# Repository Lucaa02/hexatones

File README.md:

# HEXATONES
Hexatones was born from a simple idea: to break the synthesizer down into its fundamental modules—from power supplies to VCAs, ADSR envelopes, and even guitar pedals.

Full **flexibility** is the key to discovering entirely new sounds. By stacking, cascading, and inverting modules, or by relying on smaller, granular building blocks rather than rigid, all-in-one units, Hexatones empowers musicians to explore uncharted sonic territory. 

## Open Hardware

Everybody has the right to now why and how a sound is produced. 

## Analog is Key, Digital could help

Hexatones embraces the beautiful imperfections of **analog hardware**: circuit inaccuracies, thermal drift, and the subtle inductance introduced by wiring. We reject the dullness of perfectly predictable sound. Instead, the philosophy is to lean into the system, tune into its quirks, and turn those "errors" into features to create something genuinely **unique** every single time.

## Schematics, Layout, and Panelization
Keeping costs low is a core priority. Every design is optimized to leverage **affordable** PCB fabrication services and standard component sourcing.

Got ideas to trim costs even further? Smarter layouts, tighter panelization, or clever routing? The framework is completely open dive in and make it **better**.

## Modules (Last Update October 2026)

* Power Supply Module
* 1V/Octave
* VCO
* Pseudo ADSR

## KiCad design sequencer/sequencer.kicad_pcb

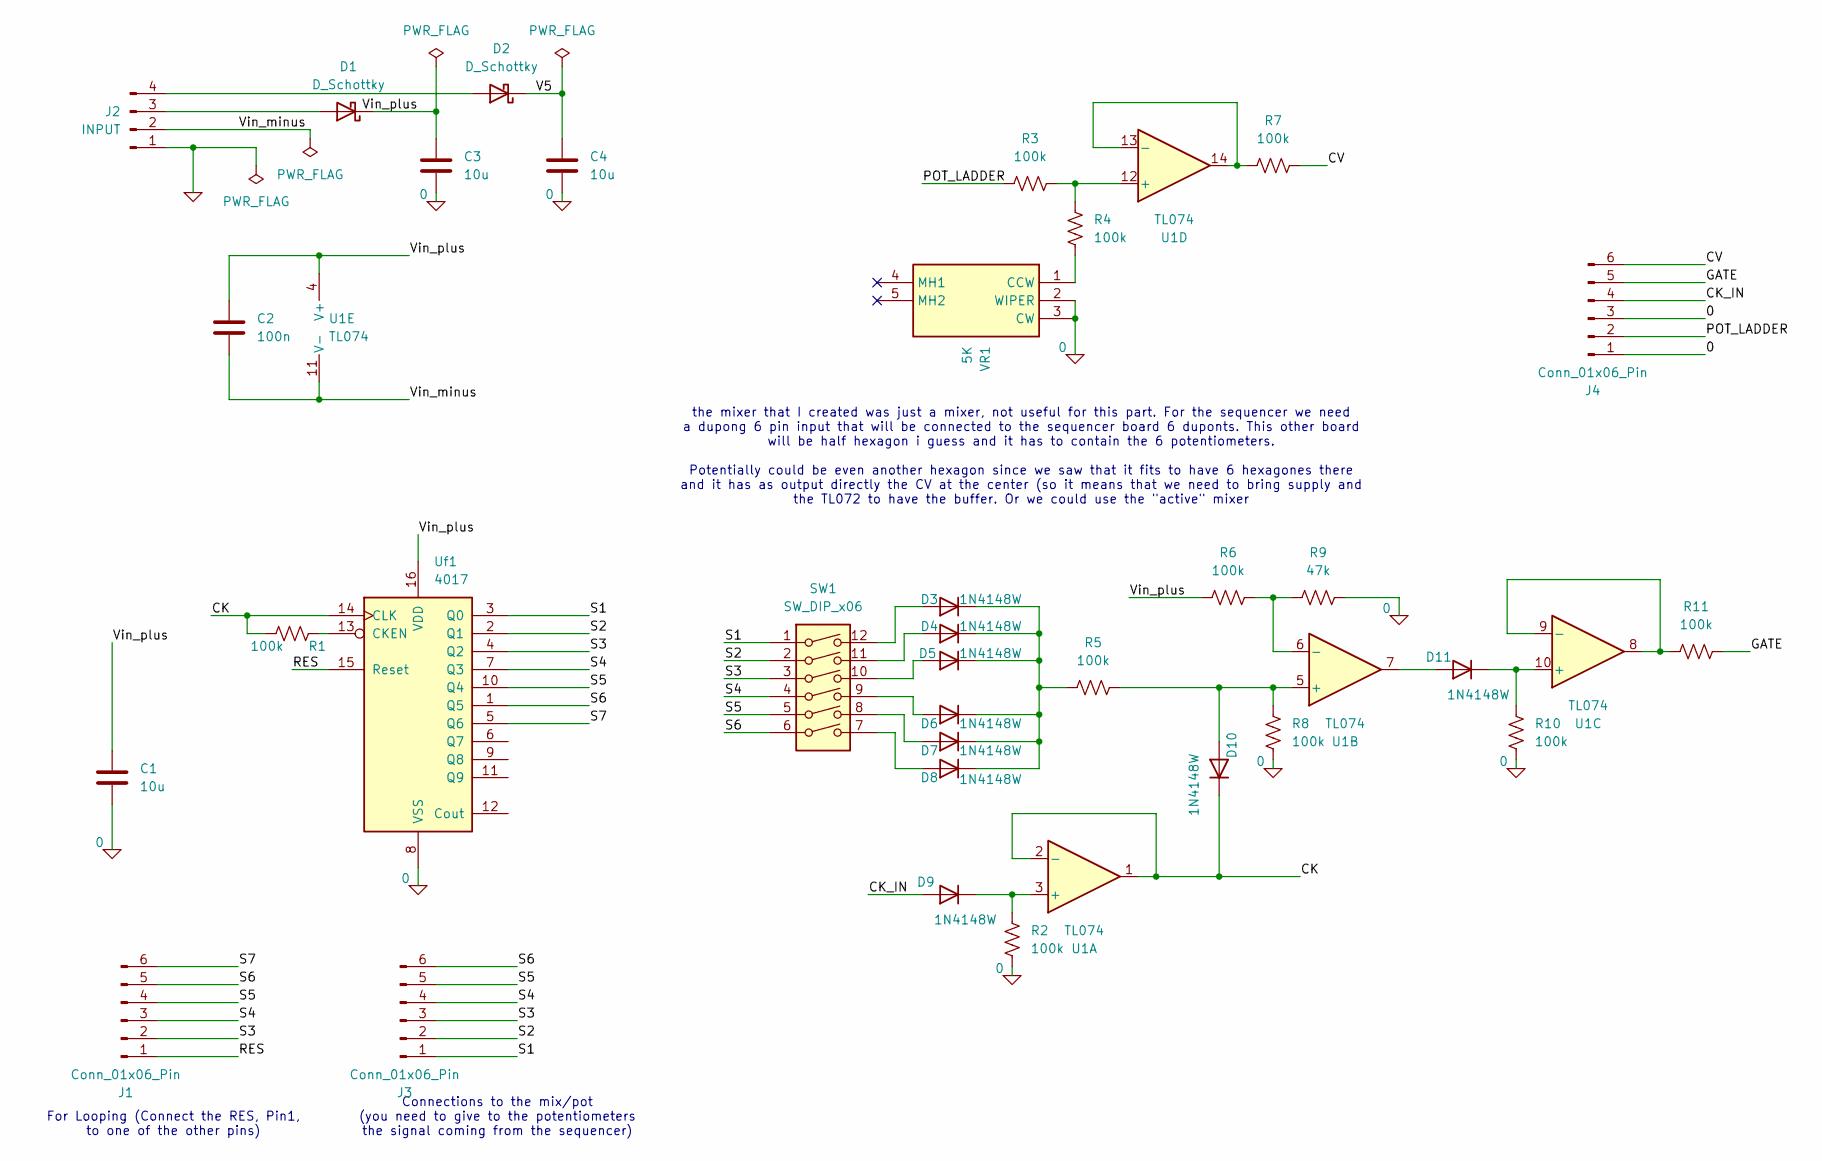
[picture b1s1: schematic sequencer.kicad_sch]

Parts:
C1, C3, C4: 10u; C_0603_1608Metric_Pad1.08x0.95mm_HandSolder
C2: 100n; C_0603_1608Metric_Pad1.08x0.95mm_HandSolder
D1, D2: D_Schottky; D_SOD-323_HandSoldering
D3, D4, D5, D6, D7, D8, D9, D10, D11: 1N4148W; D_SOD-123
J1, J3, J4: Conn_01x06_Pin; PinHeader_1x06_P2.54mm_Vertical
J2: INPUT; PinHeader_1x04_P2.54mm_Vertical
R1, R2, R3, R4, R5, R6, R7, R8, R10, R11: 100k; R_0603_1608Metric_Pad0.98x0.95mm_HandSolder
R9: 47k; R_0603_1608Metric_Pad0.98x0.95mm_HandSolder
SW1: SW_DIP_x06; SW_DIP_SPSTx06_Slide_9.78x17.42mm_W8.61mm_P2.54mm
U1: TL074; SOIC-14_3.9x8.7mm_P1.27mm
Uf1: 4017; SOIC-16_3.9x9.9mm_P1.27mm
VR1: 5K; Potentiometer_Alpha_RD901F-40-00D_Single_Vertical; Mouser Part Number 311-1940F-15R1-B100K

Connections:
0: C1.2, C3.2, C4.2, J2.1, J4.1, J4.3, R2.1, R8.1, R9.2, R10.1, Uf1.8 (VSS), VR1.2 (WIPER), VR1.3 (CW)
/CK: D10.1 (K), R1.2, U1.1, U1.2 (-), Uf1.14 (CLK)
/CK_IN: D9.2 (A), J4.4
/CV: J4.6, R7.1
/GATE: J4.5, R11.1
/POT_LADDER: J4.2, R3.2
/RES: J1.1, Uf1.15 (Reset)
/S1: J3.1, SW1.1, Uf1.3 (Q0)
/S2: J3.2, SW1.2, Uf1.2 (Q1)
/S3: J1.2, J3.3, SW1.3, Uf1.4 (Q2)
/S4: J1.3, J3.4, SW1.4, Uf1.7 (Q3)
/S5: J1.4, J3.5, SW1.5, Uf1.10 (Q4)
/S6: J1.5, J3.6, SW1.6, Uf1.1 (Q5)
/S7: J1.6, Uf1.5 (Q6)
/V5: C4.1, D2.1 (K)
/Vin_minus: C2.2, J2.2, U1.11 (V-)
/Vin_plus: C1.1, C2.1, C3.1, D1.1 (K), R6.1, U1.4 (V+), Uf1.16 (VDD)
unnamed: D1.2 (A), J2.3
unnamed: D2.2 (A), J2.4
unnamed: D3.2 (A), SW1.12
unnamed: D3.1 (K), D4.1 (K), D5.1 (K), D6.1 (K), D7.1 (K), D8.1 (K), R5.2
unnamed: D4.2 (A), SW1.11
unnamed: D5.2 (A), SW1.10
unnamed: D6.2 (A), SW1.9
unnamed: D7.2 (A), SW1.8
unnamed: D8.2 (A), SW1.7
unnamed: D9.1 (K), R2.2, U1.3 (+)
unnamed: D10.2 (A), R5.1, R8.2, U1.5 (+)
unnamed: D11.2 (A), U1.7
unnamed: D11.1 (K), R10.2, U1.10 (+)
unnamed: R6.2, R9.1, U1.6 (-)
unnamed: R11.2, U1.8, U1.9 (-)
unnamed: R3.1, R4.1, U1.12 (+)
unnamed: R7.2, U1.13 (-), U1.14
unnamed: R1.1, Uf1.13 (CKEN)
unnamed: R4.2, VR1.1 (CCW)

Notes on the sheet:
For Looping (Connect the RES, Pin1, to one of the other pins)
Connections to the mix/pot (you need to give to the potentiometers the signal coming from the sequencer)
the mixer that I created was just a mixer, not useful for this part. For the sequencer we need a dupong 6 pin input that will be connected to the sequencer board 6 duponts. This other board will be half hexagon i guess and it has to contain the 6 potentiometers. Potentially could be even another he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

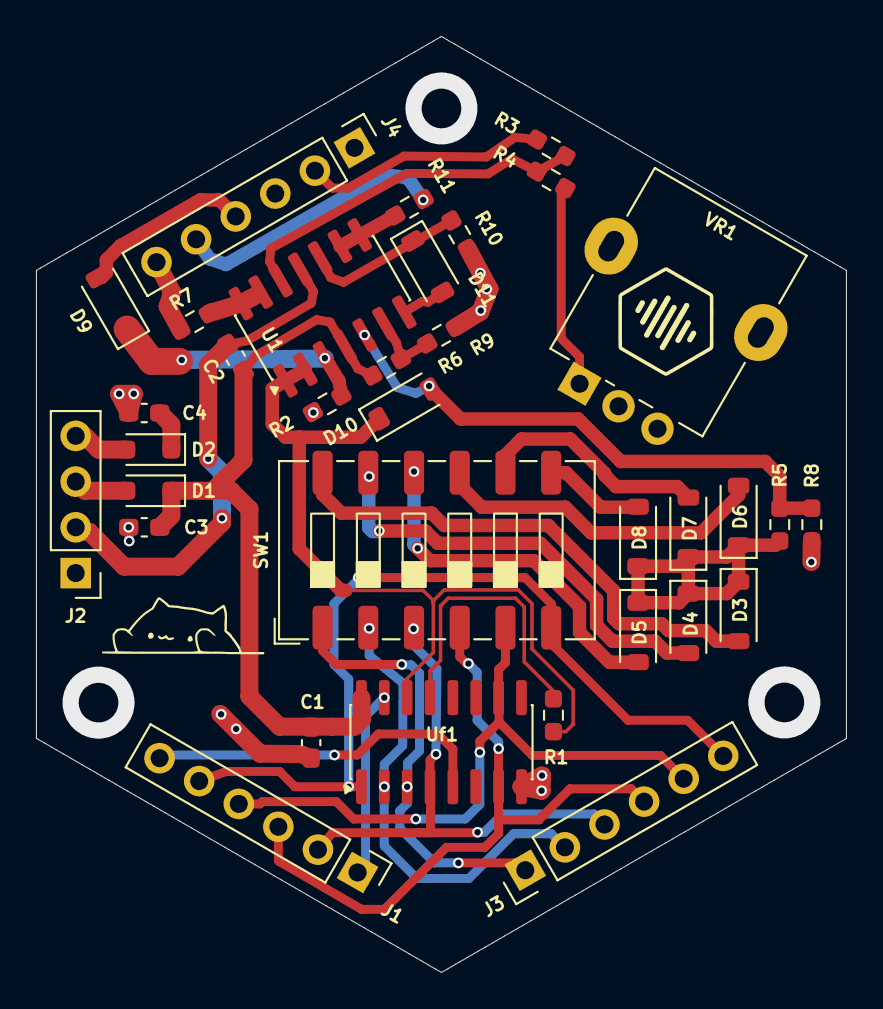
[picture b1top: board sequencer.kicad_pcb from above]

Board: 2 copper layers, 45.0 x 52.0 mm, 34 parts (0 on the bottom side), 36 nets.

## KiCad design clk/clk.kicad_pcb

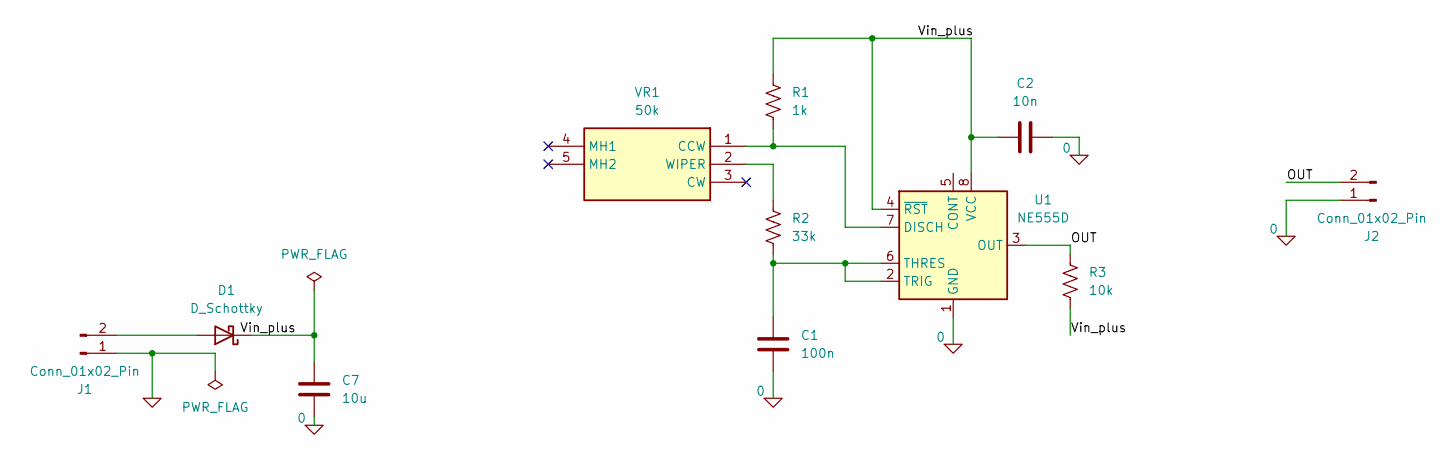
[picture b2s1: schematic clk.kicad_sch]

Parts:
C1: 100n; C_0603_1608Metric_Pad1.08x0.95mm_HandSolder
C2: 10n; C_0603_1608Metric_Pad1.08x0.95mm_HandSolder
C7: 10u; C_0603_1608Metric_Pad1.08x0.95mm_HandSolder
D1: D_Schottky; D_SOD-323_HandSoldering
J1, J2: Conn_01x02_Pin; PinHeader_1x02_P2.54mm_Vertical
R1: 1k; R_0603_1608Metric_Pad0.98x0.95mm_HandSolder
R2: 33k; R_0603_1608Metric_Pad0.98x0.95mm_HandSolder
R3: 10k; R_0603_1608Metric_Pad0.98x0.95mm_HandSolder
U1: NE555D; SOIC-8_3.9x4.9mm_P1.27mm
VR1: 50k; PinHeader_1x03_P2.54mm_Vertical; Mouser Part Number 311-1940F-15R1-B100K

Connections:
0: C1.2, C2.2, C7.2, J1.1, J2.1, U1.1 (GND)
/OUT: J2.2, R3.2, U1.3 (OUT)
/Vin_plus: C2.1, C7.1, D1.1 (K), R1.2, R3.1, U1.4 (~RST), U1.8 (VCC)
unnamed: D1.2 (A), J1.2
unnamed 4: R1.1, U1.7 (DISCH), VR1.1 (CCW); also elsewhere on the board
unnamed: C1.1, R2.1, U1.2 (TRIG), U1.6 (THRES)
unnamed 6: R2.2, VR1.2 (WIPER); also elsewhere on the board

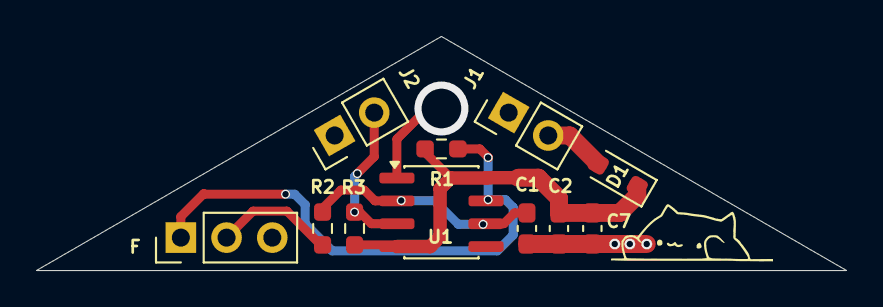
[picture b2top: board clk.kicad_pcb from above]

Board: 2 copper layers, 45.0 x 13.0 mm, 11 parts (0 on the bottom side), 7 nets.

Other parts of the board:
F: 50k; PinHeader_1x03_P2.54mm_Vertical

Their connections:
unnamed 4: F.1 (CCW); also elsewhere on the board
unnamed 6: F.2 (WIPER); also elsewhere on the board

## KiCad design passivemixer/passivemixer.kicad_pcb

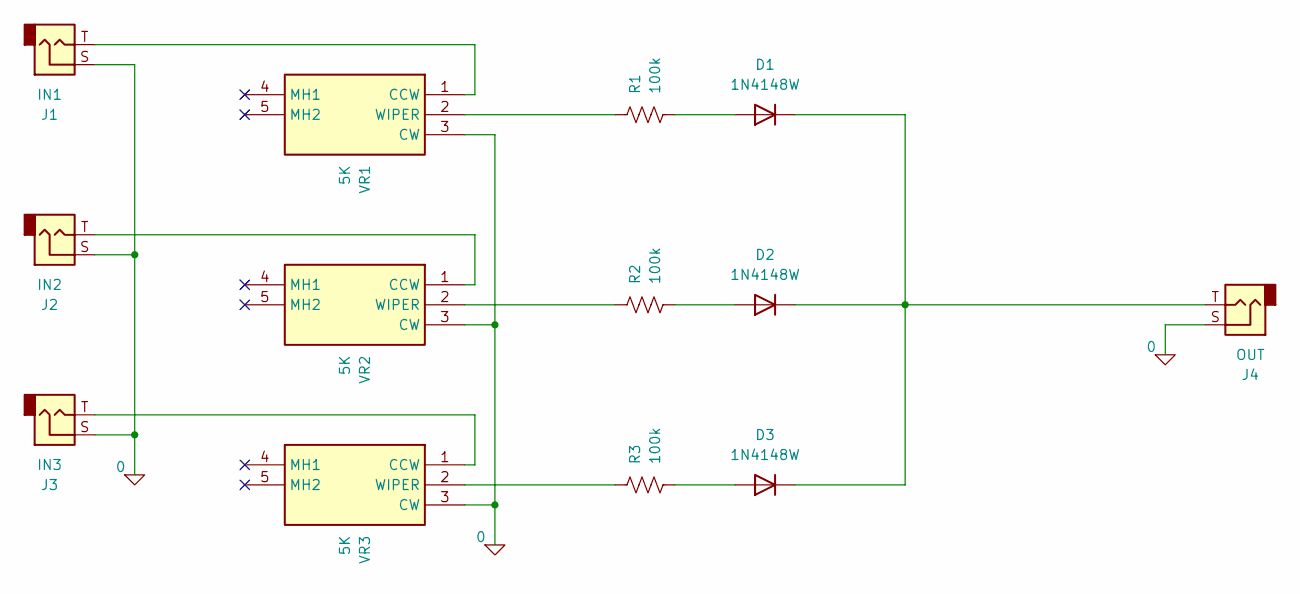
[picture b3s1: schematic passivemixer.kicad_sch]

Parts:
D1, D2, D3: 1N4148W; D_SOD-123
J1: IN1; Jack_3.5mm_QingPu_WQP-PJ398SM_Vertical_CircularHoles
J2: IN2; Jack_3.5mm_QingPu_WQP-PJ398SM_Vertical_CircularHoles
J3: IN3; Jack_3.5mm_QingPu_WQP-PJ398SM_Vertical_CircularHoles
J4: OUT; Jack_3.5mm_QingPu_WQP-PJ398SM_Vertical_CircularHoles
R1, R2, R3: 100k; R_0603_1608Metric_Pad0.98x0.95mm_HandSolder
VR1, VR2, VR3: 5K; Potentiometer_Alpha_RD901F-40-00D_Single_Vertical; Mouser Part Number 311-1940F-15R1-B100K

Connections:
0: J1.S, J2.S, J3.S, J4.S, VR1.3 (CW), VR2.3 (CW), VR3.3 (CW)
unnamed: D1.2 (A), R1.2
unnamed: D1.1 (K), D2.1 (K), D3.1 (K), J4.T
unnamed: D2.2 (A), R2.2
unnamed: D3.2 (A), R3.2
unnamed: J1.T, VR1.1 (CCW)
unnamed: R1.1, VR1.2 (WIPER)
unnamed: J2.T, VR2.1 (CCW)
unnamed: R2.1, VR2.2 (WIPER)
unnamed: J3.T, VR3.1 (CCW)
unnamed: R3.1, VR3.2 (WIPER)

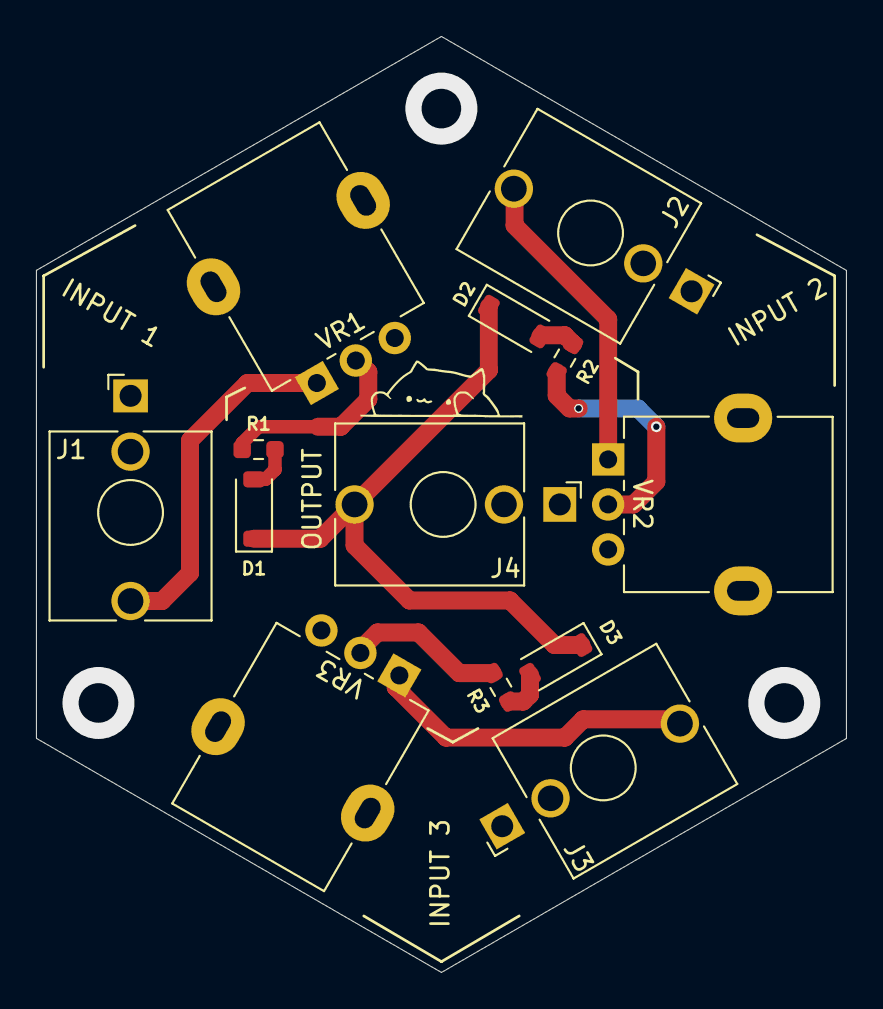
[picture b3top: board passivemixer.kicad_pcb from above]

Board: 2 copper layers, 45.0 x 52.0 mm, 13 parts (0 on the bottom side), 11 nets.

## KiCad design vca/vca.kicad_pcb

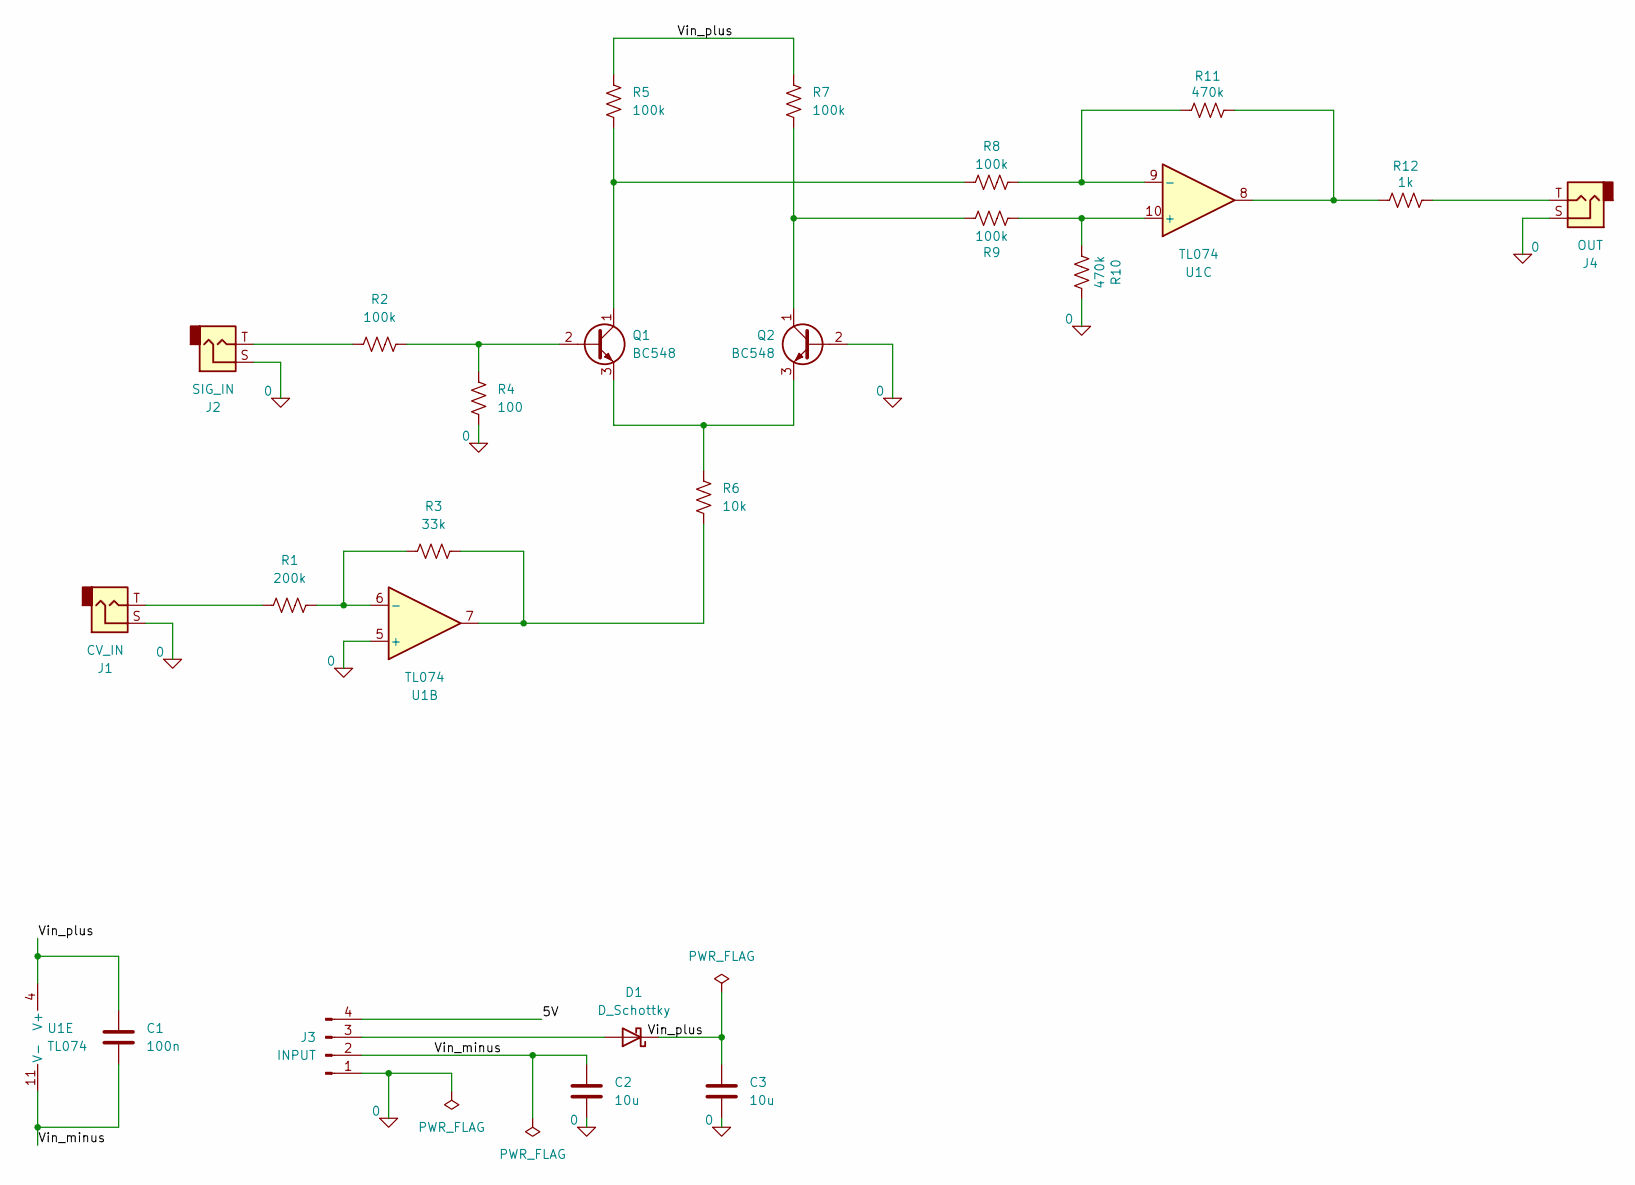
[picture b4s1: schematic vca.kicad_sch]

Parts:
C1: 100n; C_0603_1608Metric_Pad1.08x0.95mm_HandSolder
C2, C3: 10u; C_0603_1608Metric_Pad1.08x0.95mm_HandSolder
D1: D_Schottky; D_SOD-323_HandSoldering
J1: CV_IN; Jack_3.5mm_QingPu_WQP-PJ398SM_Vertical_CircularHoles
J2: SIG_IN; Jack_3.5mm_QingPu_WQP-PJ398SM_Vertical_CircularHoles
J3: INPUT; PinHeader_1x04_P2.54mm_Vertical
J4: OUT; Jack_3.5mm_QingPu_WQP-PJ398SM_Vertical_CircularHoles
Q1, Q2: BC548; TO-92_Inline
R1: 200k; R_0603_1608Metric_Pad0.98x0.95mm_HandSolder
R2, R5, R7, R8, R9: 100k; R_0603_1608Metric_Pad0.98x0.95mm_HandSolder
R3: 33k; R_0603_1608Metric_Pad0.98x0.95mm_HandSolder
R4: 100; R_0603_1608Metric_Pad0.98x0.95mm_HandSolder
R6: 10k; R_0603_1608Metric_Pad0.98x0.95mm_HandSolder
R10, R11: 470k; R_0603_1608Metric_Pad0.98x0.95mm_HandSolder
R12: 1k; R_0603_1608Metric_Pad0.98x0.95mm_HandSolder
U1: TL074; SOIC-14_3.9x8.7mm_P1.27mm

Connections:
0: C2.2, C3.2, J1.S, J2.S, J3.1, J4.S, Q2.2 (B), R4.1, R10.1, U1.5 (+)
/5V: J3.4
/Vin_minus: C1.2, C2.1, J3.2, U1.11 (V-)
/Vin_plus: C1.1, C3.1, D1.1 (K), R5.1, R7.1, U1.4 (V+)
unnamed: D1.2 (A), J3.3
unnamed: J1.T, R1.1
unnamed: J2.T, R2.2
unnamed: J4.T, R12.1
unnamed: Q1.2 (B), R2.1, R4.2
unnamed: Q1.1 (C), R5.2, R8.2
unnamed: Q1.3 (E), Q2.3 (E), R6.2
unnamed: Q2.1 (C), R7.2, R9.1
unnamed: R3.2, R6.1, U1.7
unnamed: R11.1, R12.2, U1.8
unnamed: R1.2, R3.1, U1.6 (-)
unnamed: R9.2, R10.2, U1.10 (+)
unnamed: R8.1, R11.2, U1.9 (-)

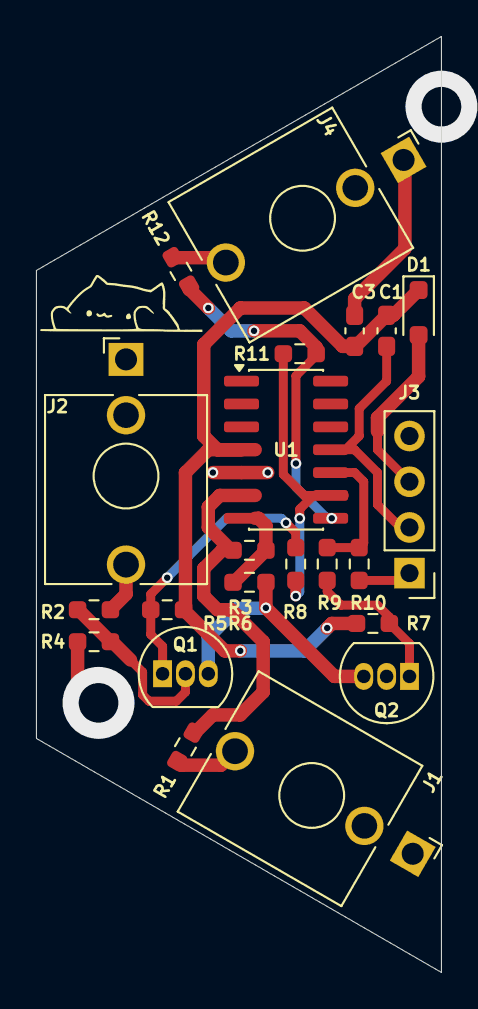
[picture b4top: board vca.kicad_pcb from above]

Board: 2 copper layers, 22.5 x 52.0 mm, 22 parts (0 on the bottom side), 16 nets.

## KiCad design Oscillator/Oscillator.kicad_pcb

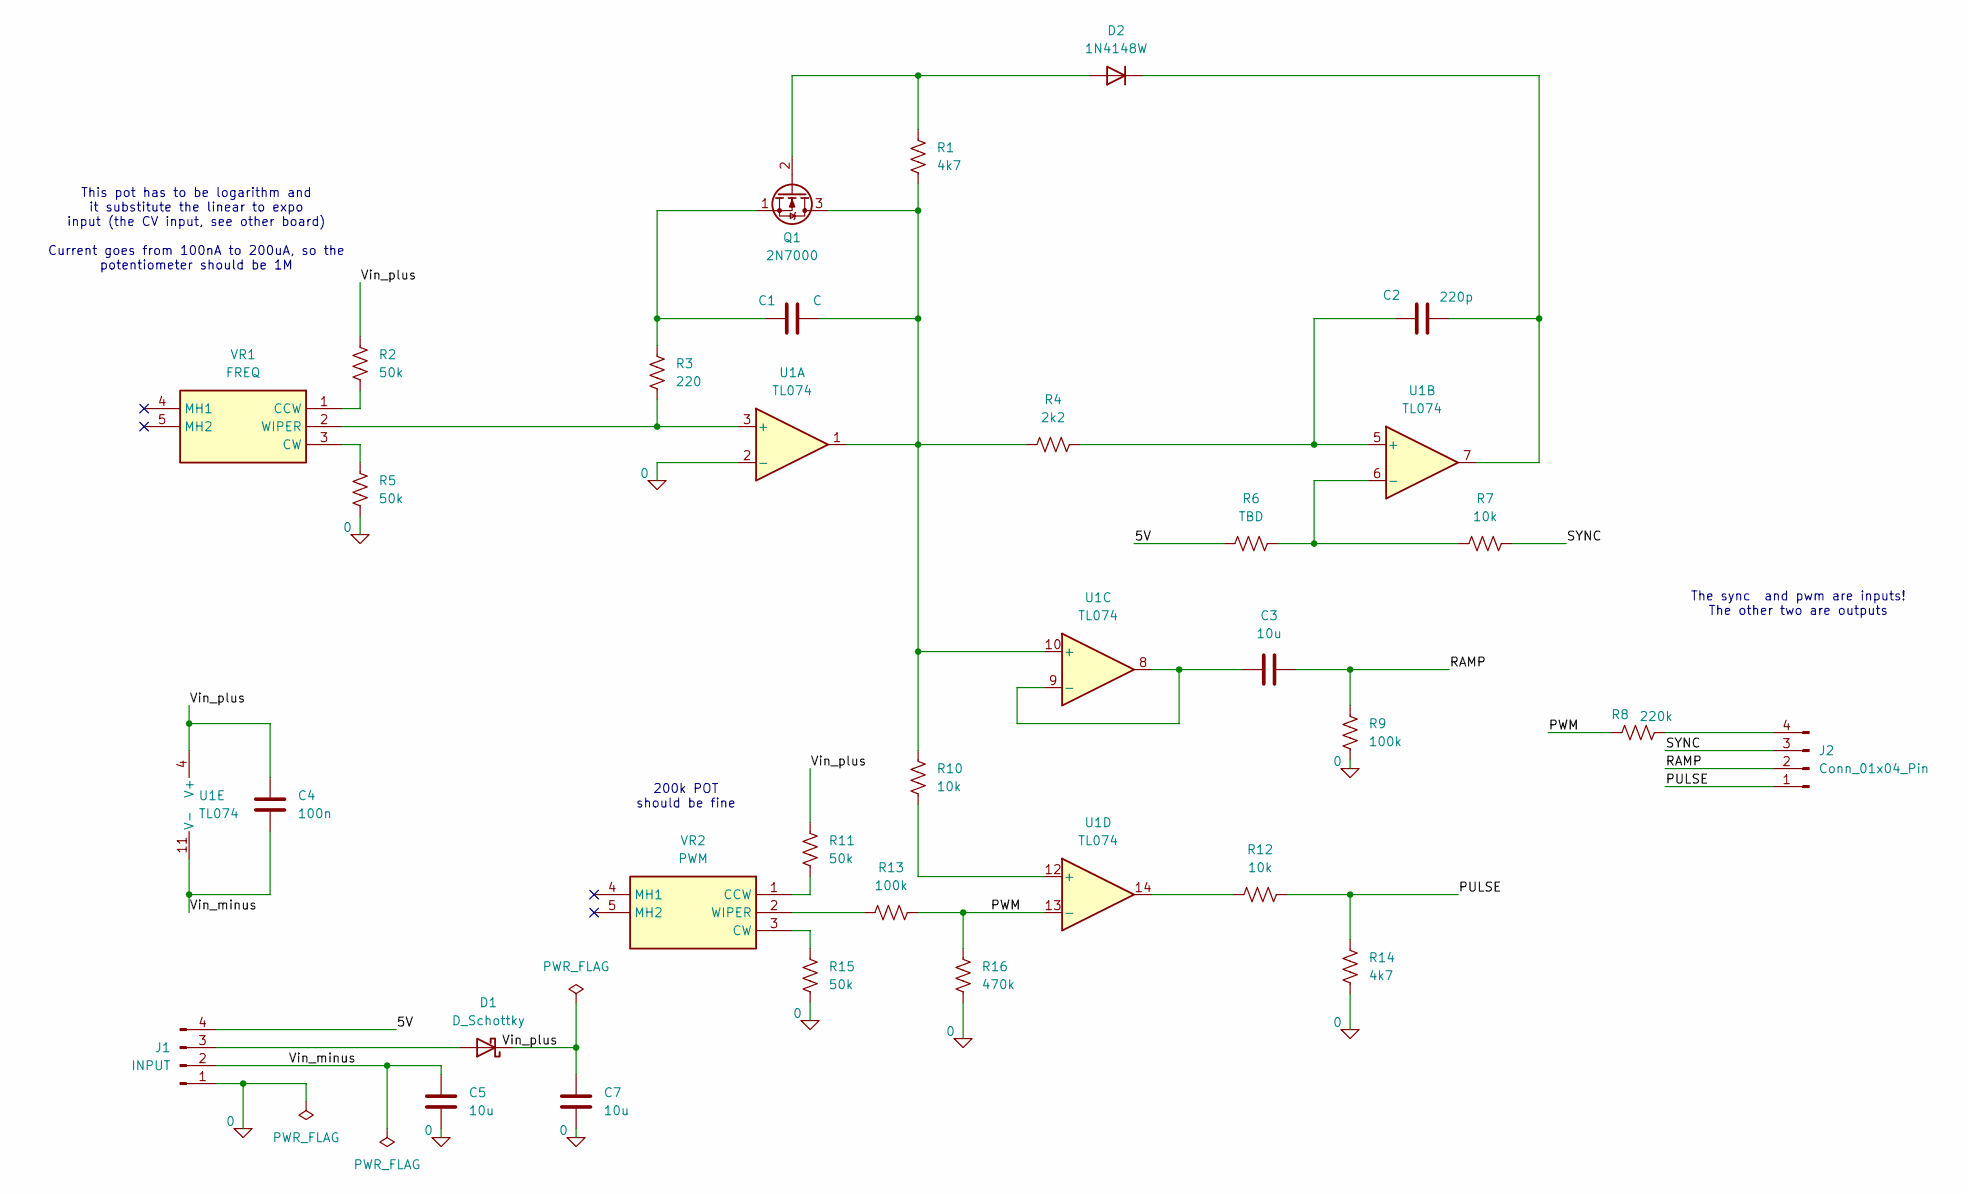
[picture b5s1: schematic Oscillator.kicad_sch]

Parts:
C1: C; C_0603_1608Metric_Pad1.08x0.95mm_HandSolder
C2: 220p; C_0603_1608Metric_Pad1.08x0.95mm_HandSolder
C3, C5, C7: 10u; C_0603_1608Metric_Pad1.08x0.95mm_HandSolder
C4: 100n; C_0603_1608Metric_Pad1.08x0.95mm_HandSolder
D1: D_Schottky; D_SOD-323_HandSoldering
D2: 1N4148W; D_SOD-123
J1: INPUT; PinHeader_1x04_P2.54mm_Vertical
J2: Conn_01x04_Pin; PinHeader_1x04_P2.54mm_Vertical
Q1: 2N7000; TO-92_Inline
R1: 4k7; C_0603_1608Metric_Pad1.08x0.95mm_HandSolder
R2, R5, R11, R15: 50k; R_0603_1608Metric_Pad0.98x0.95mm_HandSolder
R3: 220; R_0603_1608Metric_Pad0.98x0.95mm_HandSolder
R4: 2k2; R_0603_1608Metric_Pad0.98x0.95mm_HandSolder
R6: TBD; R_0603_1608Metric_Pad0.98x0.95mm_HandSolder
R7, R10, R12: 10k; R_0603_1608Metric_Pad0.98x0.95mm_HandSolder
R8: 220k; R_0603_1608Metric_Pad0.98x0.95mm_HandSolder
R9, R13: 100k; R_0603_1608Metric_Pad0.98x0.95mm_HandSolder
R14: 4k7; R_0603_1608Metric_Pad0.98x0.95mm_HandSolder
R16: 470k; R_0603_1608Metric_Pad0.98x0.95mm_HandSolder
U1: TL074; SOIC-14_3.9x8.7mm_P1.27mm
VR1: FREQ; Potentiometer_Alpha_RD901F-40-00D_Single_Vertical; Mouser Part Number 311-1940F-15R1-B100K
VR2: PWM; Potentiometer_Alpha_RD901F-40-00D_Single_Vertical; Mouser Part Number 311-1940F-15R1-B100K

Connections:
0: C5.2, C7.2, J1.1, R5.2, R9.1, R14.1, R15.2, R16.1, U1.2 (-)
/5V: J1.4, R6.1
/PULSE: J2.1, R12.1, R14.2
/PWM: R8.1, R13.2, R16.2, U1.13 (-)
/RAMP: C3.2, J2.2, R9.2
/SYNC: J2.3, R7.2
/Vin_minus: C4.2, C5.1, J1.2, U1.11 (V-)
/Vin_plus: C4.1, C7.1, D1.1 (K), R2.1, R11.1, U1.4 (V+)
unnamed: D1.2 (A), J1.3
unnamed: D2.2 (A), Q1.2 (G), R1.2
unnamed: C2.2, D2.1 (K), U1.7
unnamed: J2.4, R8.2
unnamed: C1.2, Q1.3 (D), R1.1, R4.1, R10.1, U1.1, U1.10 (+)
unnamed: C1.1, Q1.1 (S), R3.1
unnamed: R12.2, U1.14
unnamed: R3.2, U1.3 (+), VR1.2 (WIPER)
unnamed: C2.1, R4.2, U1.5 (+)
unnamed: R6.2, R7.1, U1.6 (-)
unnamed: C3.1, U1.8, U1.9 (-)
unnamed: R10.2, U1.12 (+)
unnamed: R2.2, VR1.1 (CCW)
unnamed: R5.1, VR1.3 (CW)
unnamed: R11.2, VR2.1 (CCW)
unnamed: R15.1, VR2.3 (CW)
unnamed: R13.1, VR2.2 (WIPER)

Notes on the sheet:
This pot has to be logarithm and it substitute the linear to expo input (the CV input, see other board) Current goes from 100nA to 200uA, so the potentiometer should be 1M
The sync and pwm are inputs! The other two are outputs
200k POT should be fine

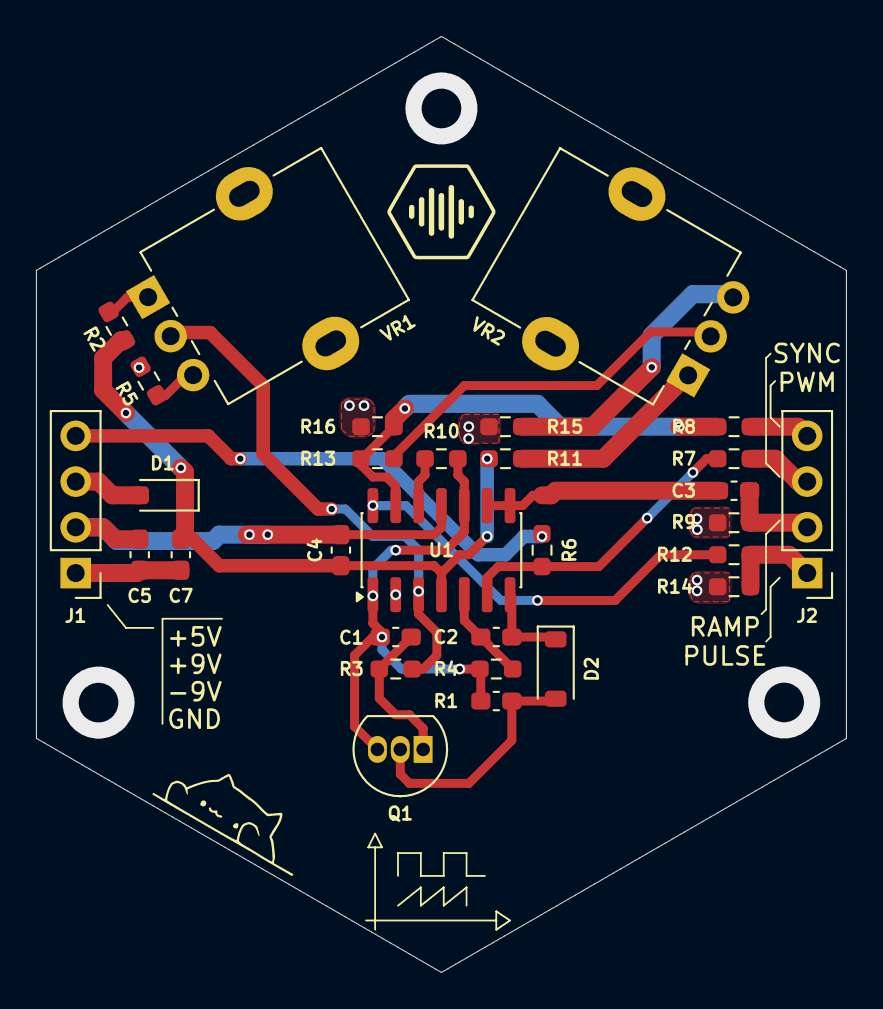
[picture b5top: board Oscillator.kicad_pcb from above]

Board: 2 copper layers, 45.0 x 52.0 mm, 30 parts (0 on the bottom side), 25 nets.

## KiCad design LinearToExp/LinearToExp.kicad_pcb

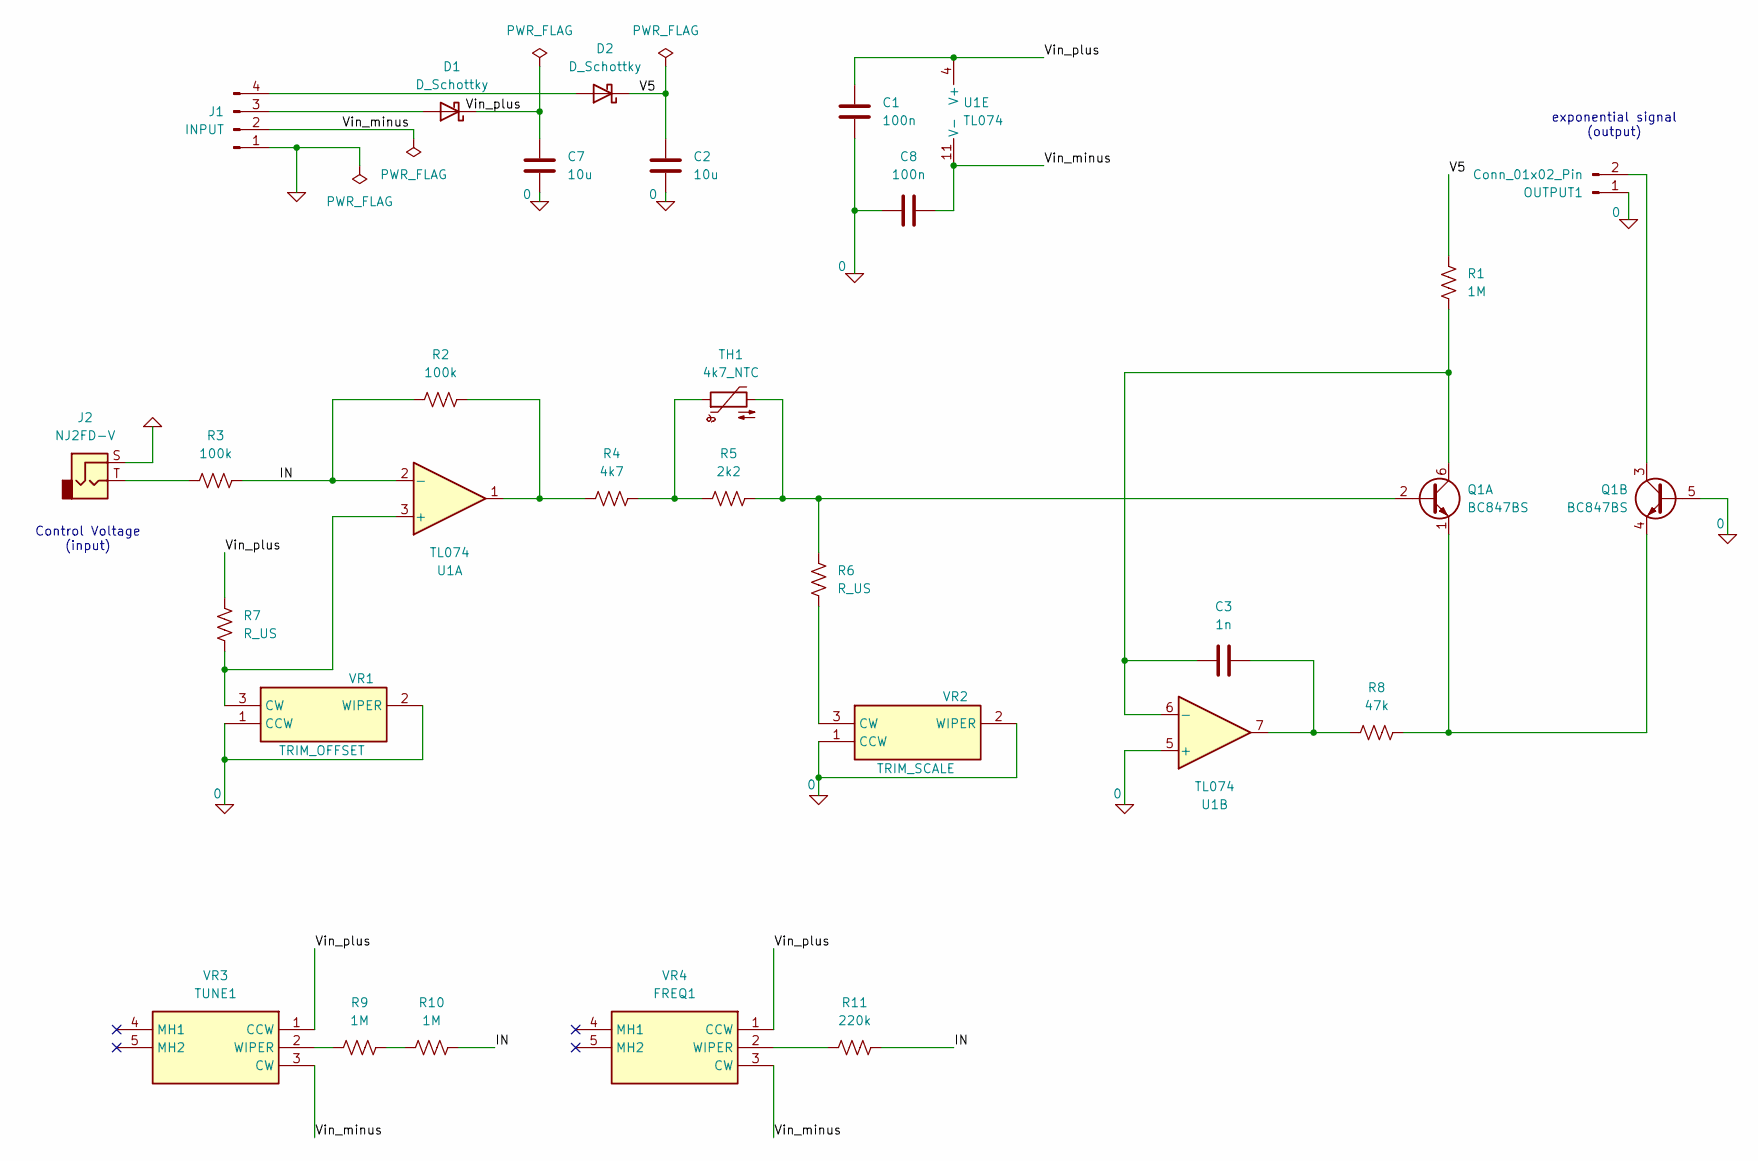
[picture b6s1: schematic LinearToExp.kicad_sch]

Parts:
C1, C8: 100n; C_0603_1608Metric_Pad1.08x0.95mm_HandSolder
C2, C7: 10u; C_0603_1608Metric_Pad1.08x0.95mm_HandSolder
C3: 1n; C_0603_1608Metric_Pad1.08x0.95mm_HandSolder
D1, D2: D_Schottky; D_SOD-323_HandSoldering
J1: INPUT; PinHeader_1x04_P2.54mm_Vertical
J2: NJ2FD-V; Jack_3.5mm_QingPu_WQP-PJ398SM_Vertical_CircularHoles
OUTPUT1: Conn_01x02_Pin; PinHeader_1x02_P2.54mm_Vertical
Q1: BC847BS; SOT-363_SC-70-6
R1, R9, R10: 1M; R_0603_1608Metric_Pad0.98x0.95mm_HandSolder
R2, R3: 100k; R_0603_1608Metric_Pad0.98x0.95mm_HandSolder
R4: 4k7; R_0603_1608Metric_Pad0.98x0.95mm_HandSolder
R5: 2k2; R_0603_1608Metric_Pad0.98x0.95mm_HandSolder
R6, R7: R_US; R_0603_1608Metric_Pad0.98x0.95mm_HandSolder
R8: 47k; R_0603_1608Metric_Pad0.98x0.95mm_HandSolder
R11: 220k; R_0603_1608Metric_Pad0.98x0.95mm_HandSolder
TH1: 4k7_NTC; R_Axial_DIN0204_L3.6mm_D1.6mm_P2.54mm_Vertical
U1: TL074; SOIC-14_3.9x8.7mm_P1.27mm
VR1: TRIM_OFFSET; Potentiometer_Bourns_3314J_Vertical; Mouser Part Number 652-3314J-1-104E
VR2: TRIM_SCALE; Potentiometer_Bourns_3314J_Vertical; Mouser Part Number 652-3314J-1-104E
VR3: TUNE1; Potentiometer_Alpha_RD901F-40-00D_Single_Vertical; Mouser Part Number 311-1940F-15R1-B100K
VR4: FREQ1; Potentiometer_Alpha_RD901F-40-00D_Single_Vertical; Mouser Part Number 311-1940F-15R1-B100K

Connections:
0: C1.2, C2.2, C7.2, C8.1, J1.1, J2.S, OUTPUT1.1, Q1.5 (B2), U1.5 (+), VR1.1 (CCW), VR1.2 (WIPER), VR2.1 (CCW), VR2.2 (WIPER)
/IN: R2.1, R3.2, R10.2, R11.2, U1.2 (-)
/V5: C2.1, D2.1 (K), R1.1
/Vin_minus: C8.2, J1.2, U1.11 (V-), VR3.3 (CW), VR4.3 (CW)
/Vin_plus: C1.1, C7.1, D1.1 (K), R7.1, U1.4 (V+), VR3.1 (CCW), VR4.1 (CCW)
unnamed: C3.2, R8.2, U1.7
unnamed: D1.2 (A), J1.3
unnamed: D2.2 (A), J1.4
unnamed: J2.T, R3.1
unnamed: OUTPUT1.2, Q1.3 (C2)
unnamed: Q1.2 (B1), R5.2, R6.2, TH1.2
unnamed: C3.1, Q1.6 (C1), R1.2, U1.6 (-)
unnamed: Q1.1 (E1), Q1.4 (E2), R8.1
unnamed: R2.2, R4.1, U1.1
unnamed: R4.2, R5.1, TH1.1
unnamed: R9.2, R10.1
unnamed: R7.2, U1.3 (+), VR1.3 (CW)
unnamed: R6.1, VR2.3 (CW)
unnamed: R9.1, VR3.2 (WIPER)
unnamed: R11.1, VR4.2 (WIPER)

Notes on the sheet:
exponential signal (output)
Control Voltage (input)

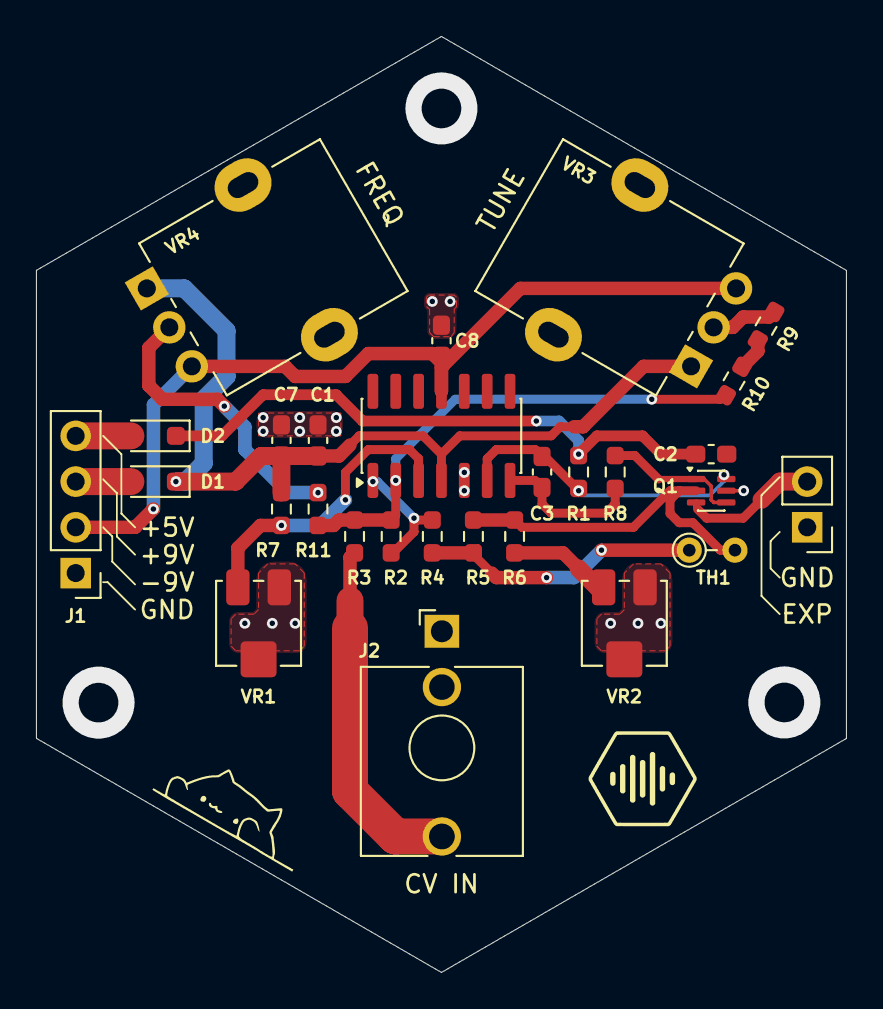
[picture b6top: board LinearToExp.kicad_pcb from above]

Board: 2 copper layers, 45.0 x 52.0 mm, 28 parts (0 on the bottom side), 20 nets.

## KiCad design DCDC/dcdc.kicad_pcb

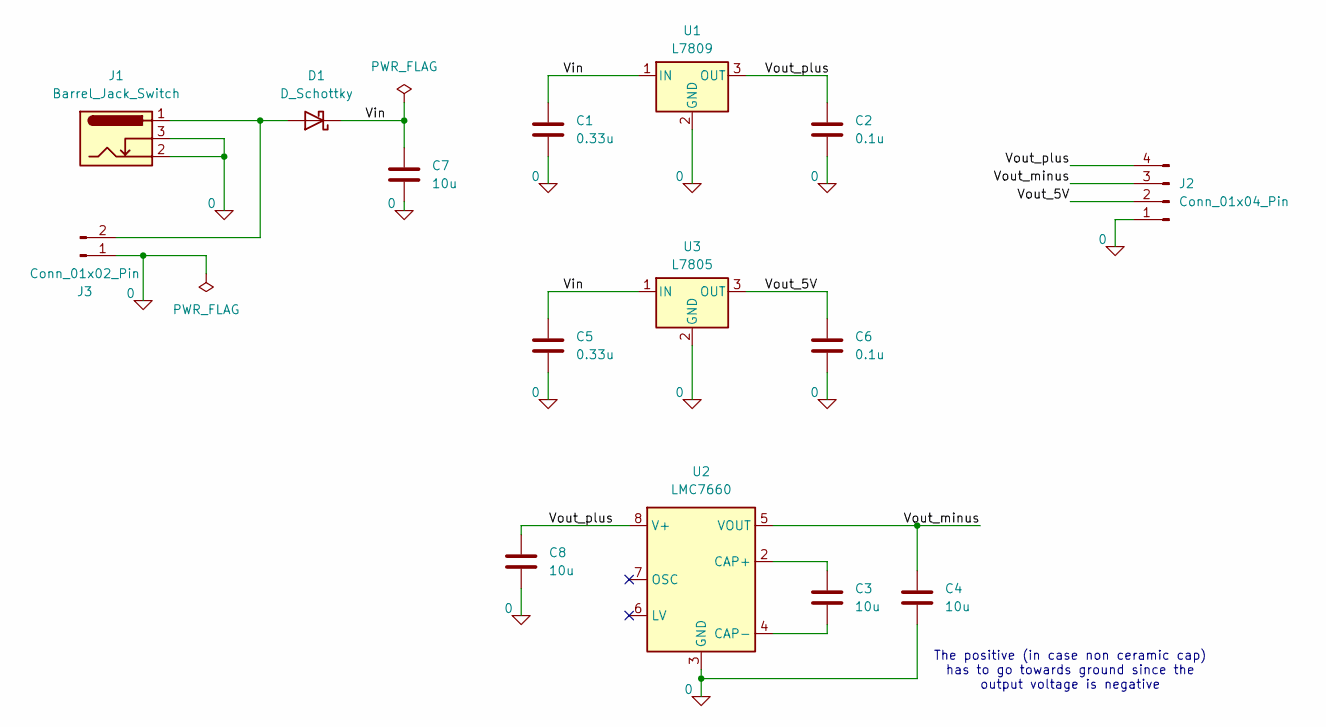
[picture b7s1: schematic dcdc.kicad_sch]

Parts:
C1, C5: 0.33u; C_0603_1608Metric_Pad1.08x0.95mm_HandSolder
C2, C6: 0.1u; C_0603_1608Metric_Pad1.08x0.95mm_HandSolder
C3, C4, C7, C8: 10u; C_0603_1608Metric_Pad1.08x0.95mm_HandSolder
D1: D_Schottky; D_SOD-323_HandSoldering
J1: Barrel_Jack_Switch; BarrelJack_Wuerth_694106106102_2.0x5.5mm
J2: Conn_01x04_Pin; PinHeader_1x04_P2.54mm_Vertical
J3: Conn_01x02_Pin; PinHeader_1x02_P2.54mm_Vertical
U1: L7809; TO-263-2
U2: LMC7660; SOIC-8_3.9x4.9mm_P1.27mm
U3: L7805; TO-263-2

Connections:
0: C1.2, C2.2, C4.2, C5.2, C6.2, C7.2, C8.2, J1.2, J1.3, J2.1, J3.1, U1.2 (GND), U2.3 (GND), U3.2 (GND)
/Vin: C1.1, C5.1, C7.1, D1.1 (K), U1.1 (IN), U3.1 (IN)
/Vout_5V: C6.1, J2.2, U3.3 (OUT)
/Vout_minus: C4.1, J2.3, U2.5 (VOUT)
/Vout_plus: C2.1, C8.1, J2.4, U1.3 (OUT), U2.8 (V+)
unnamed: D1.2 (A), J1.1, J3.2
unnamed: C3.1, U2.2 (CAP+)
unnamed: C3.2, U2.4 (CAP-)

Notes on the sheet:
The positive (in case non ceramic cap) has to go towards ground since the output voltage is negative
